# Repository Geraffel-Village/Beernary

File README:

# b33rn4rycounter
B33rn4ry Counter v2 by GeraffelVillage

https://wiki.geraffel-village.de/doku.php?id=geraffel:b33rn4ry

## Hardware V1
* based on a Atmel uC
* written is assembler

## Hardware V2
* based on RaspberryPi
* written in python
* operation separated into 2 functional boxes:
  * counter "counting and accesscontrol" (connected to the draught beer dispenser)
  * registry / cashier (Qt-Gui)

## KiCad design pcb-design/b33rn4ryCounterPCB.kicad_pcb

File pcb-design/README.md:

# b33rn4ryCounter PCB

Printed circuit board for the b33rn4ry counter.

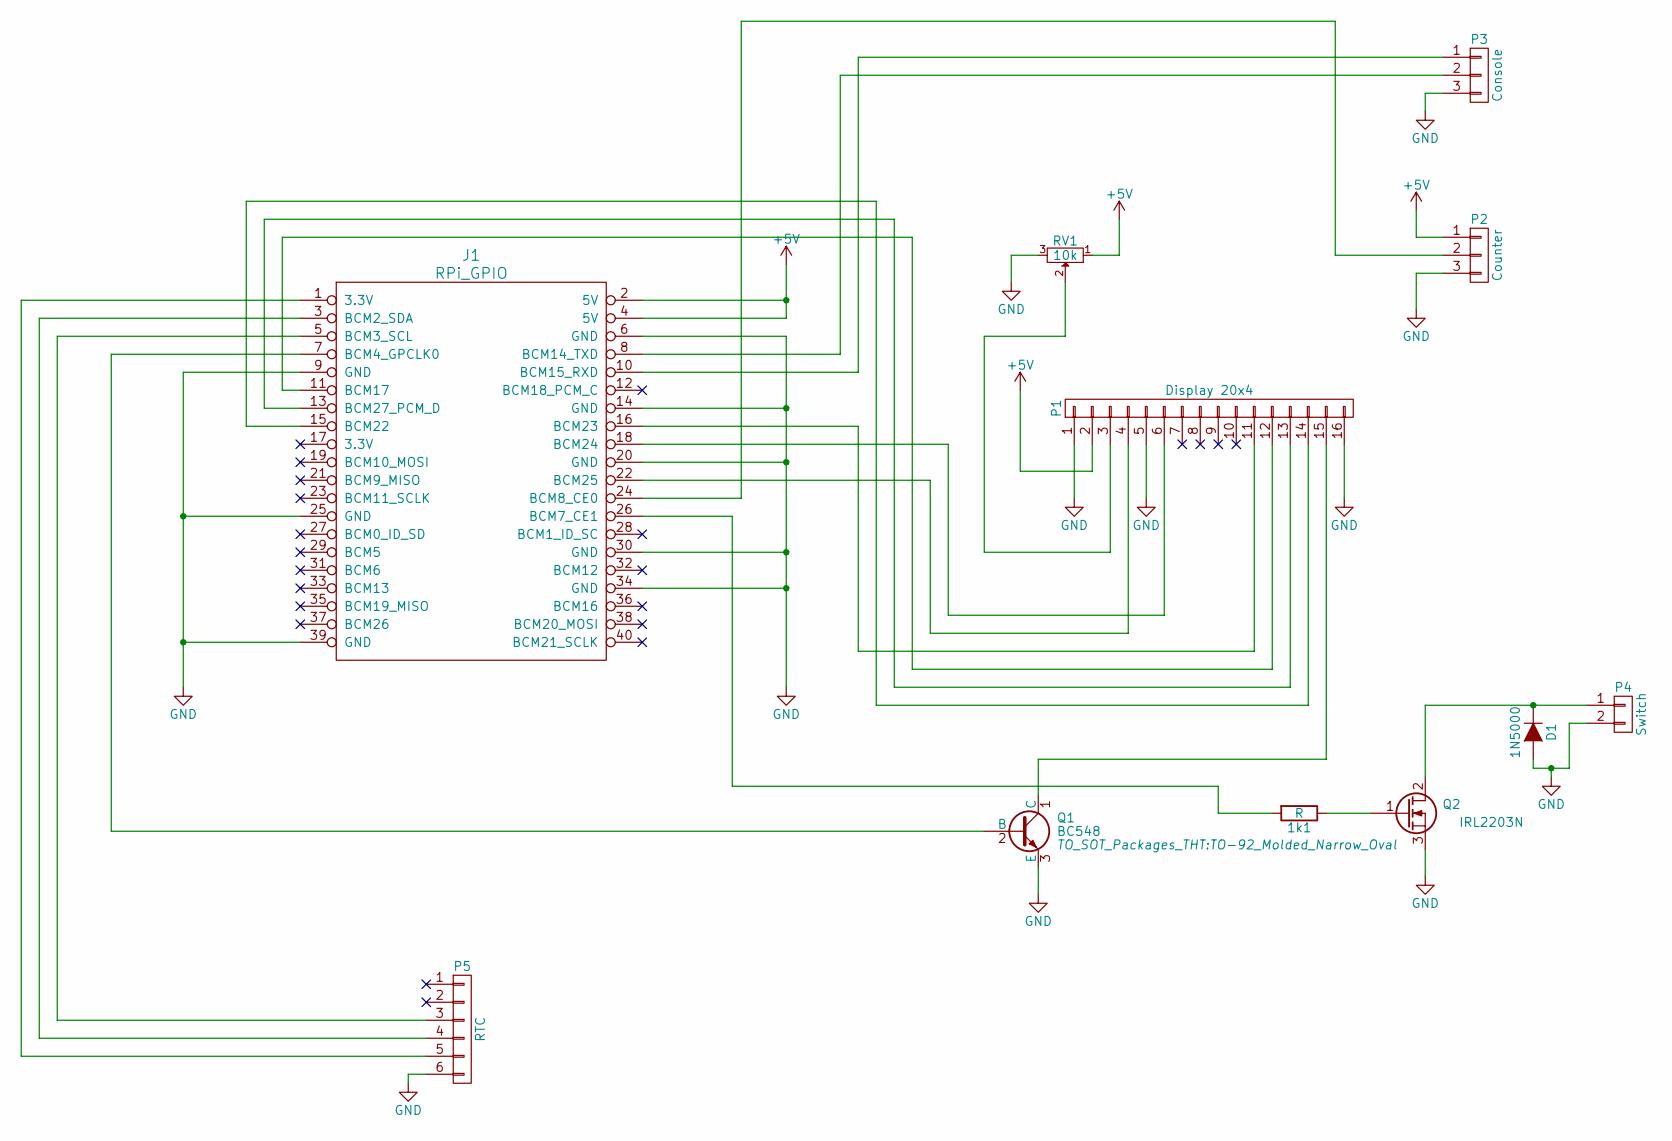
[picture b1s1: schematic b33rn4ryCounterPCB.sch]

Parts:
1k1: R; Resistor_Horizontal_RM7mm
D1: 1N5000; Diode_DO-41_SOD81_Horizontal_RM10
J1: RPi_GPIO; Pin_Header_Straight_2x20
P1: Display 20x4; Pin_Header_Angled_1x16
P2: Counter; Pin_Header_Straight_1x03
P3: Console; Pin_Header_Straight_1x03
P4: Switch; Pin_Header_Straight_1x02
P5: RTC; Pin_Header_Straight_1x06
Q1: BC548; TO-92_Molded_Narrow_Oval
Q2: IRL2203N; TO-220_Neutral123_Horizontal
RV1: 10k; Potentiometer_Bourns_3339P_Angular_ScrewUp

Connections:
+5V: J1.2 (5V), J1.4 (5V), P1.2, P2.1, RV1.1
GND: D1.2 (A), J1.6 (GND), J1.9 (GND), J1.14 (GND), J1.20 (GND), J1.25 (GND), J1.30 (GND), J1.34 (GND), J1.39 (GND), P1.1, P1.5, P1.16, P2.3, P3.3, P4.2, P5.6, Q1.3 (E), Q2.3 (S), RV1.3
unnamed: 1k1.1, Q2.1 (G)
unnamed: 1k1.2, J1.26 (BCM7_CE1)
unnamed: D1.1 (K), P4.1, Q2.2 (D)
unnamed: J1.1 (3.3V), P5.5
unnamed: J1.3 (BCM2_SDA), P5.4
unnamed: J1.5 (BCM3_SCL), P5.3
unnamed: J1.7 (BCM4_GPCLK0), Q1.2 (B)
unnamed: J1.8 (BCM14_TXD), P3.2
unnamed: J1.10 (BCM15_RXD), P3.1
unnamed: J1.11 (BCM17), P1.12
unnamed: J1.13 (BCM27_PCM_D), P1.13
unnamed: J1.15 (BCM22), P1.14
unnamed: J1.16 (BCM23), P1.11
unnamed: J1.18 (BCM24), P1.6
unnamed: J1.22 (BCM25), P1.4
unnamed: J1.24 (BCM8_CE0), P2.2
unnamed: P1.3, RV1.2
unnamed: P1.15, Q1.1 (C)

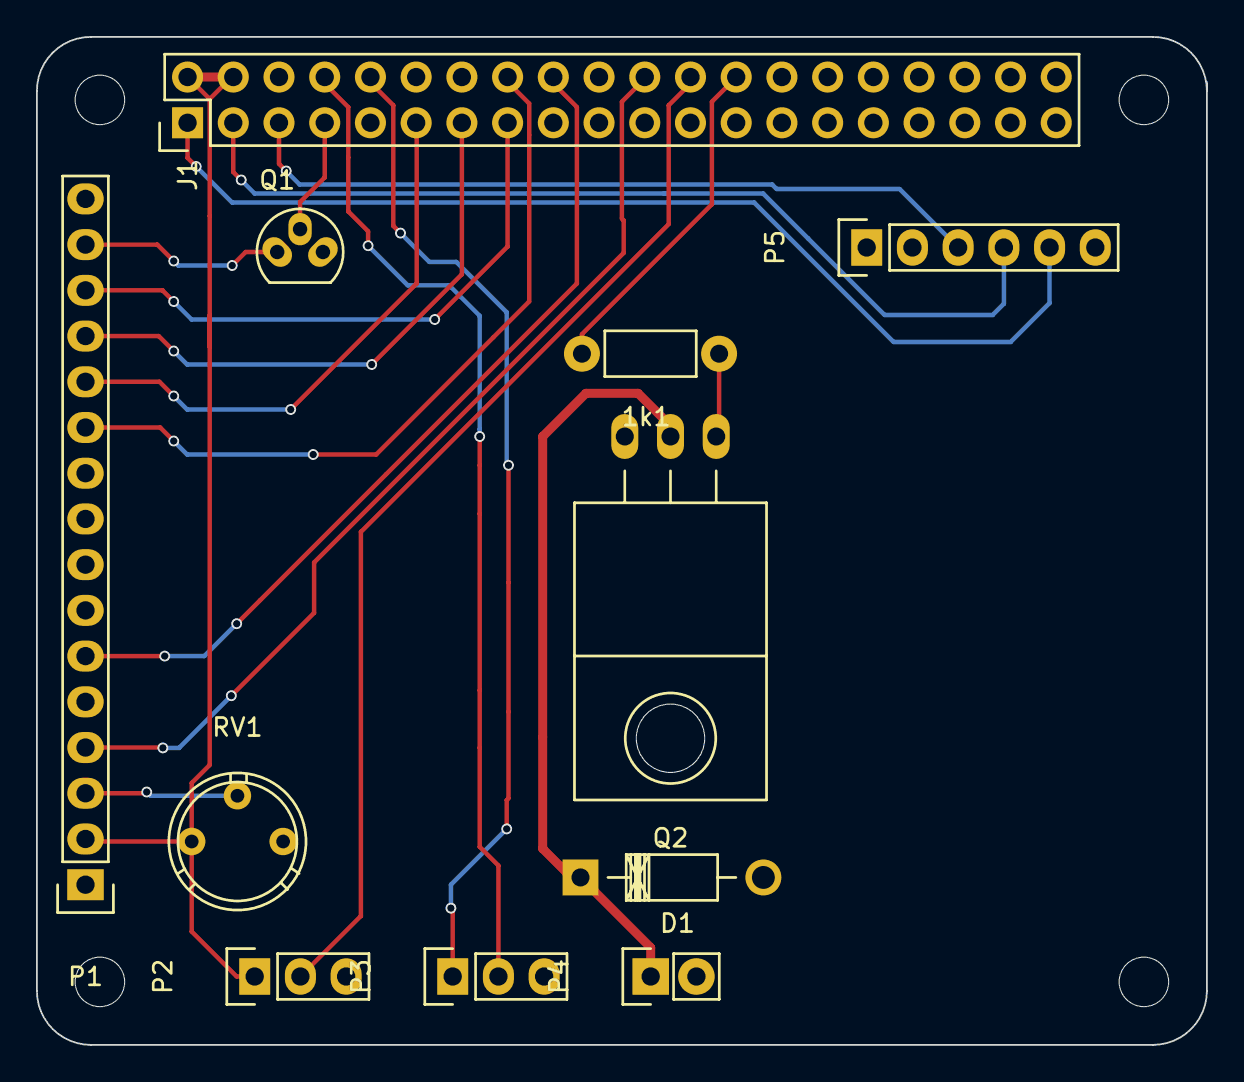
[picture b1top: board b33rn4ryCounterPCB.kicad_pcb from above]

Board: 2 copper layers, 65.0 x 56.0 mm, 11 parts (0 on the bottom side), 20 nets.

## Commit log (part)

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2015-07-29 Removed Screenshot
2015-07-29 Added new User dialog
2015-07-29 New UI
2015-07-30 Added "New User" function
2015-07-30 Rework of Add-User function
2015-08-04 Renamed to B33rn4ryRegistry
2015-08-04 Added B33rn4ryCounter Client
2015-08-04 Added B33rn4ryRegistry.py
2015-08-05 Reworked serial interface
2015-08-05 Reworked serial interfacing
2015-08-05 Removed superflous imports
2015-08-11 Adaption to RFID Reader Firmware
2015-08-11 Adapted headless binary to RFID reader
2015-08-11 Resolved variable error
2015-08-11 Deleted fragments of counting operations
2015-08-11 Corrected read_rfid routine
2015-08-11 Disabled non existent sound output
2015-08-11 Corrected indentation
2015-08-11 Minor correction
2015-08-12 Added executyble bit
2015-08-12 added basic prototype to react on pulses from flowmeter
2015-08-12 fixed shutdown to only output to LCD when pressing Ctrl-C - other failres will be reported
2015-08-12 new class "BeerKeg" to handle the Keg - a pulse from sensor will trigger the "BeerKeg.newPulse()"-member - when user logs in the variable "IdPulsesStart" will change from None to pulses counted for t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
2015-08-12 fix calculation us users pulses
2015-08-12 refactored all database-access to class Beern4ryDatabase - setting dbtype to 'MYSQL' or 'FILE'
2015-08-12 refactored database-access into separate class (B33rn4ryDatabase) - this class will offload the work to class ('FILE', 'MYSQL')
2015-08-12 added storeDraft() to database - to store drafted volume per user
2015-08-13 removed 300 debounce -setting on flowsensor input - checked for function by BusPirate swtiching and Mics-impulse-rotary-switch
2015-08-13 added List "validUsers" for IDs to grant access
2015-08-13 FIX: when switching to "IDLE" also calculate volume
2015-08-13 added shebang
2015-08-13 correcting SQL-statments + MySql-calls
2015-08-13 the authed user is stored in "IDtmp"
2015-08-13 switching to "MYSQL"-database on production-BC
2015-08-13 the pulldown for the flowsensor is installed in connector-hardware, so disabling it in SoC
2015-08-13 included init-style boot-script
2015-08-13 added database.getKegPulses() & database.setKegPulses to be able to count on the whole keg - current Keg-pulses will be stored at every end of a draft-process
2015-08-13 included dump of database structure
2015-08-14 - some changes to use "B33rn4ryDatabase.py" also - add "service"-menu - add some basic function to handle keg-swap
2015-08-14 removed some debug info from addUser()
2015-08-14 fixed detection of dublicate ID / user in addUser()
2015-08-14 implemented addng a new keg - setting the _ONLY_ nonempty keg of the event to "isempty=true" - adding a new keg with 0 pulses and "isempty=False" to this event
2015-08-14 added tab to select the event you work on in Servicemenu - selected eventid is stored in "window.currentEvent"
2015-08-14 added setting of active event via B33rn4ryRegistry when selecting and event database.setEventActive() sets teh new flag "selected" in the database
2015-08-14 added funcions to find the active Event & active keg (for Counter) - Database.getCurrentKeg() - Database.getActiveEvent() added some exceptions to signal problems to caller - B33rn4rySetupEventError 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
2015-08-14 added Event-detection & Keg-detection to B33rn4ryCounter - also print message on display in case of error
2015-08-15 -fix call of B33rn4ryExceptions -loading of pulses of keg on startup -implemeting detection of new connected keg (via oldKegID)
2015-08-15 moved check for new keg to end of loop
2015-08-15 cleanup of some messages
2015-10-02 Added code from CCCamp back to github repo for B33rn4ryCounter
2017-08-01 Fix mySQL error
2017-08-05 B33rn4ryCounter: add some syslog-output
2017-08-05 B33rn4ryCounter: split reader-handling from main-code
    new file B33rn4ryReader.py with class "UabRfid"
    - to interface with the USB-based RFID-reader
2019-07-19 B33rn4ryReader: fix log-message when initializing Serial-reader
2019-07-27 dellete B33rn4ryDatabase.pyc
2019-07-28 remove unneeded .pyc files from repo and update .gitignore
2019-07-30 add a basic README
2019-07-30 B33rn4ryCounter.py: a bit of cleanup
2019-07-30 B33rn4ryDatabase.py: a bit of cleanup
2019-07-30 B33rn4ryReader.py: a bit of cleanup
2019-07-30 Cleanup of really unused code
2019-07-30 B33rn4ryExceptions: some words for documentation
2019-07-30 B33rn4ryDatabase: documant the main-methods of the B33rn4ryDatabase-class
    The B33rn4ryDatabase should be instantiated by the external caller only, where the concrete database-type should be provided also. This class internally takes care of managing the actual database and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
2019-07-30 B33rn4ryReader: add some documentation of the actual classes doing the rfid-reader communication
    The class B33rn4ryReader provides two sub-classes:
    * B33rn4ryReader.UsbRfid
    * B33rn4ryReader.SerialRfid
2019-08-06 convert to Python3 (via 2to3)
    Convert the current code to Python3 by using 2to3 script.
2019-08-06 B33rn4ryCounter: fix a space / tab mismatch
    complains after converting to python3
2019-08-06 B33rn4ryDatabase: readd value for NotImplementedError
    readd explaining message, that was removed by 2to3
2019-08-06 fix imports
    relative imports are not supported
2019-08-07 Update GPIOs according to Mic's settings
2019-08-07 B33rnaryCounter: cosmetic changes by Mic
    * also improve display-output
2019-08-07 Move hard coded credentials to config file
2019-08-07 move reading of configfile into B33rn4ryCounter.py
    having the configparsing in the Database-class makes it less reusable
2019-08-07 B33rn4ryReader: fix reading / decoding of tagID for serial-reader
    as per datashee we receive the TagID and a checksum from the reader,
    like "data:F004414A2E; cksum:D". The first and last byte of data seem
    rubbish, so we keep "data:004414A2". This hex-value we just need to
    convert to integer to get our ID (as read from the USB-reader).
    Using the correct values also seems to make the checksum-code working
    as the fail messages are gone.
2019-08-13 Also use mySQL config settings for Registry
2019-08-21 B33rn4ryCounter: turn on backlight on WelcomeScreen
2019-08-21 config: add net options for comports of counter and registry
2019-08-21 B33rn4ryCounter: read serial-device from config-file
2019-08-21 config.ini: move to contrib folder as example-file
    Having this file tracked by git will not make it ignored, even it's
    listed in .gitignore. Moving it into the subfolder will prevent
    it from causing conflicts based in local changes to the actual
    used config.ini file.
2019-08-21 B33rn4ryRegistry: also implement reading of config.ini
2019-08-21 Registry: refactor reading of serial-device
    move reading of configuration into main() and push settings
    (database, device for reader) into the classes as needed.
2019-08-21 B33rn4ryRegistry: refresh userlist on formular-loading
    This is required, as of the later DB-initialization
2019-08-21 B33rn4ryReader: fix return-value of reading for serialreader
    since some time an uninitialized value was returned. Have it
    returning "tagdata"
2019-08-21 B33rn4ryReader: remove useless debug
2019-08-21 B33rn4ryReader: read data from reader directly into "data" and "cksum" variables
2019-08-21 B33rn4ryReader: disable checksum-tesing
2019-08-21 B33rn4ryCounter: fix testing for access
    convert the interger-representation of the tagid into it's 4-byte
    hex-representation to compare with Database-IDs
2019-08-21 B33rn4ryRegistry: update ID-string put into DB to have no header
2019-08-21 B33rn4ryRegistry: use B33rn4ryReader class to access the rfid-reader
2019-08-21 B33rn4ryReader: usb_rfid: have it return only the TAG-ID
    do not return the header + id. this makes it compatible to the
    serial-reader results.
2019-08-21 B33rn4ryDatabase: do not fail on adding 1st keg of an event
    current code was failing, because on a new event will be no keg
    to be marked as empty. So do not raise an error when there is no
    keg defined.
2019-08-21 implemtent deleteUser in B33rn4ryDatabase
    and also use this mentod in B33rn4ryRegistry
2019-08-21 B33rn4ryExceptions: create DatabaseException & ReaderCommError
2019-08-21 use B33rn4ryDatabaseException in Registry and Database
2022-07-23 B33rn4ryReader: fix datatype-errors and disable non-functional checksumming for serialreader
2022-07-23 B33rn4ryCounter: update com-port and DB-credentials to new deployed hardware
2022-07-23 Added drafting timeout
2023-07-25 use correct GIO-pin for flowmeter
2023-08-06 counter-board: add Arduino-code for hardware-level pulse-counting
    We are not sure, if the RPi will count the pulses fast enough or lose some,
    So there is an additional Arduino hooked up in parallel to do this.
    We use a "Metro mini" (Atmega328 16MHz), connected via its build-in USB.
2023-08-12 Commit v2.1 initial
2023-08-12 Commit v2.1 initial (#23)
2023-08-14 Chaos Camp 2023: release 2.1
2023-08-14 Chaos Camp 2023: release 2.1 (#27)
2023-08-14 Rename README to README.md
2023-08-14 Rename counter subsystem
2023-08-14 Rename counter subsystem (#28)
2023-08-15 Add seconds valve implementation
2023-08-16 Add second valve implementation (#29)
    * Add seconds valve implementation
    * PROD customizing
    ---------
2023-08-16 Extent README
2023-08-16 Extent README (#31)
2023-08-16 Fix shutdown routine
2023-08-16 Fix shutdown routine (#32)
2023-08-16 Fix exception for shutdown
2023-08-16 Add new tool to read RFID
2023-08-16 Fix USB reader implementation
2023-08-16 Decrease restart time
2023-08-16 Add local RFID reader tool (#33)
    * Fix exception for shutdown
    * Add new tool to read RFID
    * Fix USB reader implementation
    * Decrease restart time
    ---------
2023-08-16 Ensure deployment also works on default Debian 11
2023-08-16 Ensure deployment also works on default Debian 11 (#35)
2023-08-16 Fix SIGTERM handler
2023-08-16 Fix SIGTERM handler (#36)
2023-08-16 Fix display
2023-08-16 Fix display (#38)
2023-08-16 Fix missing tap in metrics push call
2023-08-16 Fix log message
2023-08-16 Add metrics collection with InfluxDB
2023-08-16 Downgrade to influxdb 1.8
    As 2.0 does not run on 32 bits hardware
2023-08-16 Implement mocking of classes for physical devices
    So that we can run the code without any special hardware
2023-08-17 Add metrics collection with InfluxDB (#34)
    * Add metrics collection with InfluxDB
    * Fix missing tap in metrics push call
    * Fix log message
    * Downgrade to influxdb 1.8
    As 2.0 does not run on 32 bits hardware
2023-08-17 Add metrics collection with InfluxDB (#34)
    * Add metrics collection with InfluxDB
    * Fix missing tap in metrics push call
    * Fix log message
    * Downgrade to influxdb 1.8
    As 2.0 does not run on 32 bits hardware
2023-08-17 Implement mocking of classes for physical devices (#37)
    So that we can run the code without any special hardware
2023-08-17 Fix InfluxDB escaping
2023-08-17 Fix InfluxDB escaping (#41)
2023-08-17 Fix config parsing and reader initialization
2023-08-17 Fix config parsing and reader initialization (#43)
2023-08-17 Fix grafana bootstrapping
    Service grafana-server was not started
2023-08-17 Fix webhook shutdown
2023-08-17 Fix webhook shutdown (#45)
2023-08-17 Fix identation error
2023-08-17 Second try to fix grafana bootstrapping
2023-08-17 Second try to fix grafana bootstrapping (#46)
2023-08-18 Fix webhook parsing
2023-08-18 Wait for grafana service on initial deployment
2023-08-18 Fix webhook ID
2023-08-18 Fix p3ki handling
2023-08-18 Enable Grafana public dashboard
2023-08-24 Add screenshot of Grafana dashboard
2023-08-24 Add public Grafana dashboard
2023-08-25 Add screenshot of Grafana dashboard (#50)
2023-08-25 Enable Grafana public dashboard (#49)
    * Enable Grafana public dashboard
    * Add public Grafana dashboard
2025-08-09 feat
2025-08-09 WHY2025 Production Sync
2025-08-09 Attempt to fix display timing issues
2025-08-09 Avoid D6 (GPIO 27) for display. Temporary workaround to bisect issues.
2025-08-09 fix signal light LED color mapping to be more intuitive
2025-08-09 support webhook auth w/ threads
2025-08-09 Enable metrics
2025-08-11 Remove display threading lock
2025-08-11 Add sleep in webhook auth, avoiding the method to be called too frequently
